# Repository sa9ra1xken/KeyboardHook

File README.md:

# Objective

This project aims to remodel a 1980s electronic typewriter into an online terminal in order to recreate the computing environment of the 1970s.
The project uses a Canon electronic typewriter Model S-14 which employs a daisy-wheel impact printing mechanism, manufactured in 1986.

# Technical approrch

It looks the keyboard is the only available device to order printing operation, my aproach is to interfare the keyboard matrix with additionaly equipped switing device. 
An Arduino-based controller manipulates CMOS analog switches placed between scan lines and sense lines of the keyboard matrix to print characters sent from a host computer.
The controller also monitors user input by tracking behavior on the scan and sense lines, and transmits the input characters to the host.

# keyboard matrix and scan code

The keyboard matrix consists of eight scan lines and eight sense lines. Each key are maped on a pair of one scan line and one sense line. Each scan line is sequencially activated one by one. The controler knows which key is pressed by checking the sense line state at the timing each scan line is activated. 
The following table shows the key mapping in the matrix on the unit. 

|scan\sense|pin12(COL0)|pin11(COL1)|pin10(COL2)|pin9(COL3)|pin8(COL4)|pin7(COL5)|pin6(COL6)|pin5(COL7)|
|:---------:|:--------:|:---------:|:---------:|:--------:|:--------:|:--------:|:--------:|:--------:|
|pin21(ROW0)|REP       |A          |I          |Q         |Y         |6         |/         |TAB       |
|pin20(ROW1)|SHIFT     |B          |J          |R         |Z         |7         |^         |DEL       |
|pin19(ROW2)|LOCK      |C          |K          |S         |0         |8         |-         |REPEAT    |
|pin18(ROW3)|          |D          |L          |T         |1         |9         |=         |BS        |
|pin17(ROW4)|          |E          |M          |U         |2         |,         |β         |CODE      |
|pin16(ROW5)|          |F          |N          |V         |3         |.         |          |          |
|pin15(ROW6)|          |G          |O          |W         |4         |,         |°         |          |
|pin14(ROW7)|          |H          |P          |X         |5         |.         |space     |          |

In the Arduino internal process, a key press is represented by the intermediate byte of information called the scan code.
Below is the bit structure of the scan code.

|Bit7|Bit6|Bit5|Bit4|Bit3|bit2|Bit1|Bit0|
|----|----|----|----|----|----|----|----|
|0   |0   |C[2]|C[1]|C[0]|R[2]|R[1]|R[0]|

C[i] means bit i in the binary encoded colmn number, R[j] means bit j in the binary encoded row number.

# Handshaking

Since the printing speed of the typewriter is usually much slower than the host computer, we have to implement some mechanism to synchronaize the data rate between them. The mechanism makes the host computer wait sending character untile the typewriter has processed the last character.
In order to know the state of mechanical behavior in the typewriter, a couple of logic signal on the embeded controller IC7 (HD6301Y) on the main typewriter control board are monitored by the adapter. I have discoverd these signals by some oscilloscoping.

|Signal|Function|Connection to Arduino|
|------|--------|---------------------|
|IC7.Pin24|Goes low while typing a character|D3|
|IC7.Pin16|Goes high while feeding paper|D7|

Regarding the handshaking between Arduino and the host, I initially intended to use the CTS signal on the serial port, but I couldn't get the host side to handle CTS-based handshaking. I decided to use ACK-based handshaking,   where Arduino sends back an ACK character (0x06) upon processing a character from the host.

# Printing usupported characters

Because the typewriter was originally not intended to be used with computers, several characters defined in the ASCII code table were missing. To cope with this limitation, I have implemented a method to express unsupported characters by overtyping multiple caracters. 
Below shows the unsupported characters and the replaced overtyping combination I used. 

|Original character|Replacement|
|------------------|-----------|
|'<'               |'(' and '-'|
|'>'               |')' and '-'|
|'{'               |'(' and '='|
|'}'               |')' and '='|
|'['               |'(' and '_'|
|']'               |')' and '_'|
 
# Inputting unsupported characters 

There is a special button named CODE on the keyboard.

The original function of the button is to bring the typewriter into special mode in which you can change some operating parameters such as Left and Right Margins, TAB position, character pitch, etc. I named the mode "CODE mode".         
Since pressing any of the alphabet keys when the typewriter is in CODE mode doesn't make printing action, I used CODE mode for inputting the unsupported characters and some ASCII control codes. Below shows the key functions in CODE mode I implemented.

|Key      |Function in CODE mode     |
|---------|--------------------------|
|B        |Send CTRL-B (STX) to host |
|C        |Send CTRL-C (ETX) to host |
|D        |Send CTRL-D (EOT) to host |
|E        |Send CTRL-E (ENQ) to host |
|F        |Send CTRL-F (ESC) to host |
|J        |behaves as '<' key        |
|K        |behaves as '>' key        |
|L        |behaves as '[' key        |
|L with SHIFT|behaves as '{' key        | 
|M        |behaves as ']' key        |
|M with SHIFT|behaves as '}' key        |  

By the way, though pressing alphabet keys in CODE mode doesn't print, some variation in behavior results, as shown in the following table. Program code in Arduino absorbs these variations.  

|Key|Behavior in CODE mode|
|--|:---|
|A|sounds beep|
|B|Print a blank character then exit CODE mode|
|C|sounds beep and exits CODE mode|
|D-I|sounds beep|
|J-M|Do nothing and exit CODE mode|
|N-Z|sounds beep|

# Sumary of adapter interface

|pin#|in/out|signal function    |main board connection  |
|----|------|-------------------|-----------------------|
|1   |      |                   |                       |
|2   |      |                   |                       |
|3   |in    |+feed in progress  |IC7.Pin16              |
|4   |      |                   |                       |
|5   |      |                   |                       |
|6   |      |                   |                       |
|7   |in    |-print in progress |IC7.pin24              |
|8   |pass. |KBD matrix ROW0    |FFC.pin21              |
|9   |pass. |KBD matrix ROW1    |FFC.pin20              |
|10  |pass. |KBD matrix ROW2    |FFC.pin19              |
|11  |pass. |KBD matrix ROW3    |FFC.pin18              |
|12  |pass. |KBD matrix ROW4    |FFC.pin17              |
|13  |pass. |KBD matrix ROW6    |FFC.pin16              |
|14  |pass. |KBD matrix ROW6    |FFC.pin15              |
|15  |pass. |KBD matrix ROW7    |FFC.pin14              |
|16  |pass. |KBD matrix COL0    |FFC.pin13              |
|17  |pass. |KBD matrix COL1    |FFC.pin12              |
|18  |pass. |KBD matrix COL2    |FFC.pin11              |
|19  |pass. |KBD matrix COL3    |FFC.pin10              |
|20  |pass. |KBD matrix COL4    |FFC.pin9               |
|21  |pass. |KBD matrix COL5    |FFC.pin8               |
|22  |pass. |KBD matrix COL6    |FFC.pin7               |
|23  |pass. |KBD matrix COL7    |FFC.pin6               |
|24  |power |ground             |FFC.pin5               |
|25  |      |                   |FFC.pin4               |
|26  |in    |-shift lock        |FFC.pin3               |
|27  |in    |-CODE mode         |FFC.pin2               |
|28  |power |power supply(+5V)  |FFC.pin1               |

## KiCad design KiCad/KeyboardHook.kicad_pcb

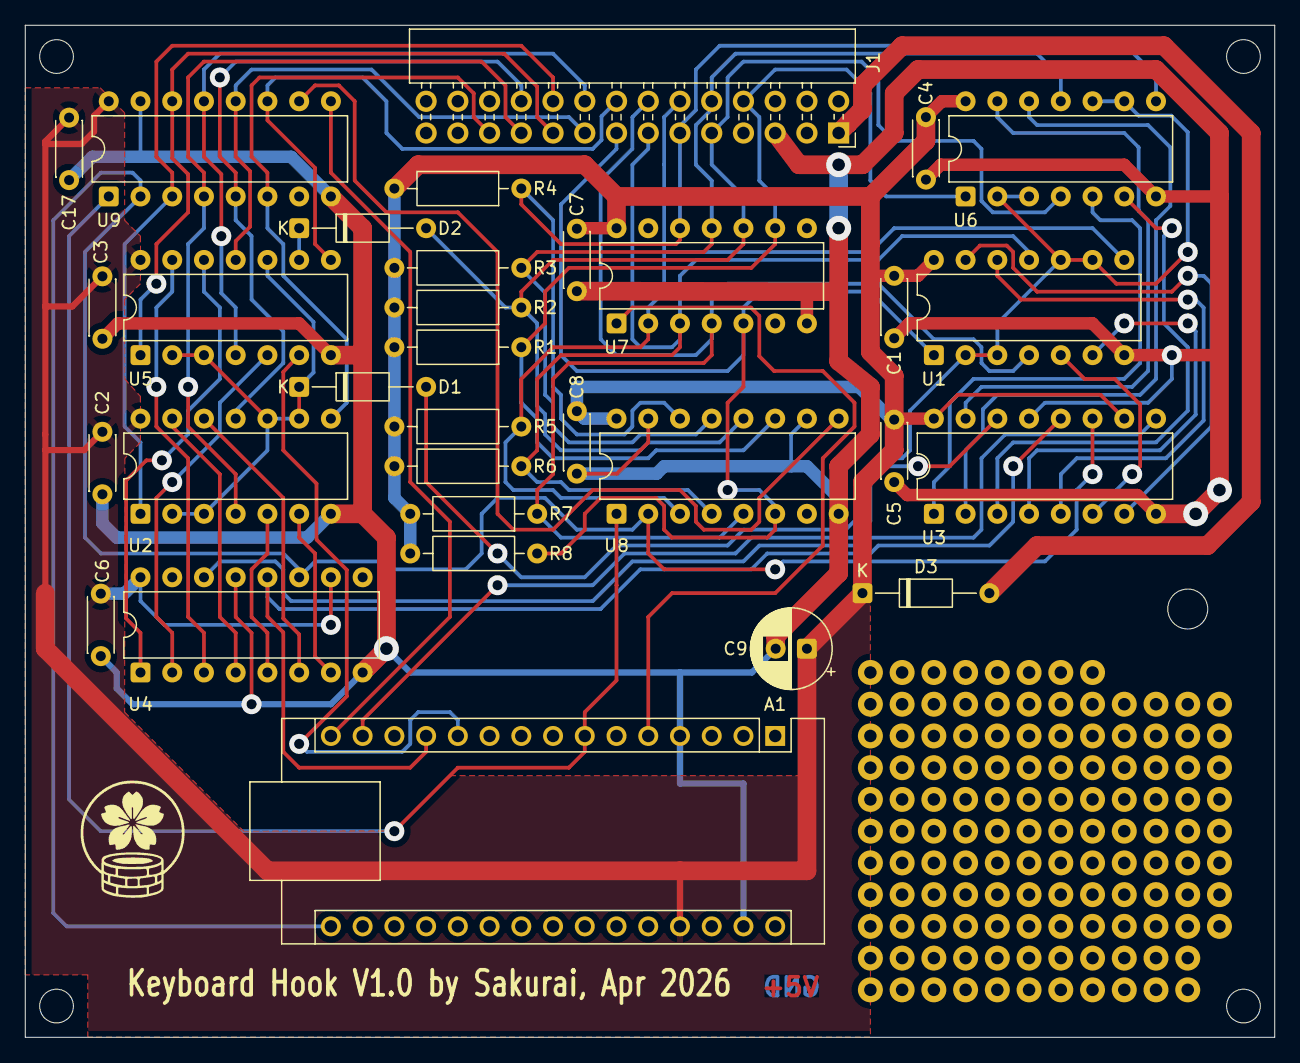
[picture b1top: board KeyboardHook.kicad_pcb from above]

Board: 2 copper layers, 100.0 x 81.0 mm, 32 parts (0 on the bottom side), 46 nets.

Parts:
A1: Arduino_Nano_v2.x; Arduino_Nano
C1, C2, C3, C4, C5, C6, C7, C8, C17: 100n; C_Disc_D4.3mm_W1.9mm_P5.00mm
C9: C_Polarized; CP_Radial_D6.3mm_P2.50mm
D1, D2: BAW75; D_DO-35_SOD27_P10.16mm_Horizontal
D3: D_Schottky; D_DO-35_SOD27_P10.16mm_Horizontal
J1: Conn_02x14_Odd_Even; PinSocket_2x14_P2.54mm_Horizontal
R1, R2, R3, R4, R5, R6, R7, R8: 10K; R_Axial_DIN0207_L6.3mm_D2.5mm_P10.16mm_Horizontal
U1, U2, U5, U6: CD4066BE; DIP-14_W7.62mm
U3, U4: 74HC595; DIP-16_W7.62mm
U7: 4068; DIP-14_W7.62mm
U8, U9: 74HC165; DIP-16_W7.62mm

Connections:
+5V: A1.27 (+5V), C1.1, C2.1, C3.1, C4.1, C5.1, C6.1, C7.2, C8.2, C9.1, C17.2, D3.1 (K), R1.2, R2.2, R3.2, R4.2, R5.2, R6.2, R7.2, R8.2, U1.14 (V_{DD}), U2.14 (V_{DD}), U3.10 (~SRCLR), U3.16 (VCC), U4.10 (~SRCLR), U4.16 (VCC), U5.14 (V_{DD}), U6.14 (V_{DD}), U7.14 (Vdd), U8.16 (VCC), U9.16 (VCC)
+5V_DEV: D3.2 (A), J1.1
/COL0: J1.16, U5.8, U9.11 (D0)
/COL1: J1.17, U5.11, U9.12 (D1)
/COL2: J1.18, U5.4, U9.13 (D2)
/COL3: J1.19, U5.1, U9.14 (D3)
/COL4: J1.20, U2.1, U9.3 (D4)
/COL5: J1.21, U2.4, U9.4 (D5)
/COL6: J1.22, U2.11, U9.5 (D6)
/COL7: J1.23, U2.8, U9.6 (D7)
/ROW0: J1.8, R1.1, U6.1, U7.9 (E), U8.11 (D0)
/ROW1: D2.2 (A), J1.9, R2.1, U6.4, U7.10 (F), U8.12 (D1)
/ROW2: J1.10, R3.1, U6.11, U7.11 (G), U8.13 (D2)
/ROW3: J1.11, R4.1, U6.8, U7.12 (H), U8.14 (D3)
/ROW4: J1.12, R5.1, U1.8, U7.2 (A), U8.3 (D4)
/ROW5: J1.13, R6.1, U1.11, U7.3 (B), U8.4 (D5)
/ROW6: J1.14, R7.1, U1.4, U7.4 (C), U8.5 (D6)
/ROW7: J1.15, R8.1, U1.1, U7.5 (D), U8.6 (D7)
/switch listener/CLK: A1.16 (D13), U3.11 (SRCLK), U4.11 (SRCLK), U8.2 (CP), U9.2 (CP)
/switch listener/MISO: A1.15 (D12), U9.9 (Q7)
/switch listener/N_INT: A1.5 (D2), U7.1 (K)
/switch listener/READ: A1.7 (D4), U8.1 (~PL), U9.1 (~PL)
/switch pusher/LOAD: A1.12 (D9), U3.12 (RCLK), U4.12 (RCLK)
/switch pusher/MOSI: A1.14 (D11), U3.14 (SER)
/switch pusher/SEL_COL1: U4.1 (QB), U5.12
/switch pusher/SEL_COL2: U4.2 (QC), U5.5
/switch pusher/SEL_COL3: U4.3 (QD), U5.13
/switch pusher/SEL_COL4: U2.13, U4.4 (QE)
/switch pusher/SEL_COL5: U2.5, U4.5 (QF)
/switch pusher/SEL_COL6: U2.12, U4.6 (QG)
/switch pusher/SEL_COL7: U2.6, U4.7 (QH)
/switch pusher/SEL_ROW0: U3.15 (QA), U6.13
/switch pusher/SEL_ROW1: U3.1 (QB), U6.5
/switch pusher/SEL_ROW2: U3.2 (QC), U6.12
/switch pusher/SEL_ROW3: U3.3 (QD), U6.6
/switch pusher/SEL_ROW4: U1.6, U3.4 (QE)
/switch pusher/SEL_ROW5: U1.12, U3.5 (QF)
/switch pusher/SEL_ROW6: U1.5, U3.6 (QG)
/switch pusher/SEL_ROW7: U1.13, U3.7 (QH)
/switch pusher/SHIFT: A1.11 (D8), U5.6
GND: A1.4 (GND), A1.29 (GND), C1.2, C2.2, C3.2, C4.2, C5.2, C6.2, C7.1, C8.1, C9.2, C17.1, J1.5, U1.7 (V_{SS}), U2.7 (V_{SS}), U3.8 (GND), U3.13 (~OE), U4.8 (GND), U4.13 (~OE), U5.7 (V_{SS}), U6.7 (V_{SS}), U7.7 (Vss), U8.8 (GND), U8.10 (DS), U8.15 (~CE), U9.8 (GND), U9.15 (~CE)
unnamed: D1.2 (A), U1.2, U1.3, U1.9, U1.10, U6.2, U6.3, U6.9, U6.10
unnamed: D1.1 (K), U2.2, U2.3, U2.9, U2.10, U5.2, U5.3, U5.10
unnamed: D2.1 (K), U5.9
unnamed: U3.9 (SO), U4.14 (SER)
unnamed: U8.9 (Q7), U9.10 (DS)

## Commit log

2026-06-19 Components for converting a Canon S-14 typewriter to a teletype
2026-06-29 MD file editted.
2026-06-29 MD file renamed.
2026-06-29 MD recovered
2026-06-29 removed old sketch
2026-06-30 readme correction
